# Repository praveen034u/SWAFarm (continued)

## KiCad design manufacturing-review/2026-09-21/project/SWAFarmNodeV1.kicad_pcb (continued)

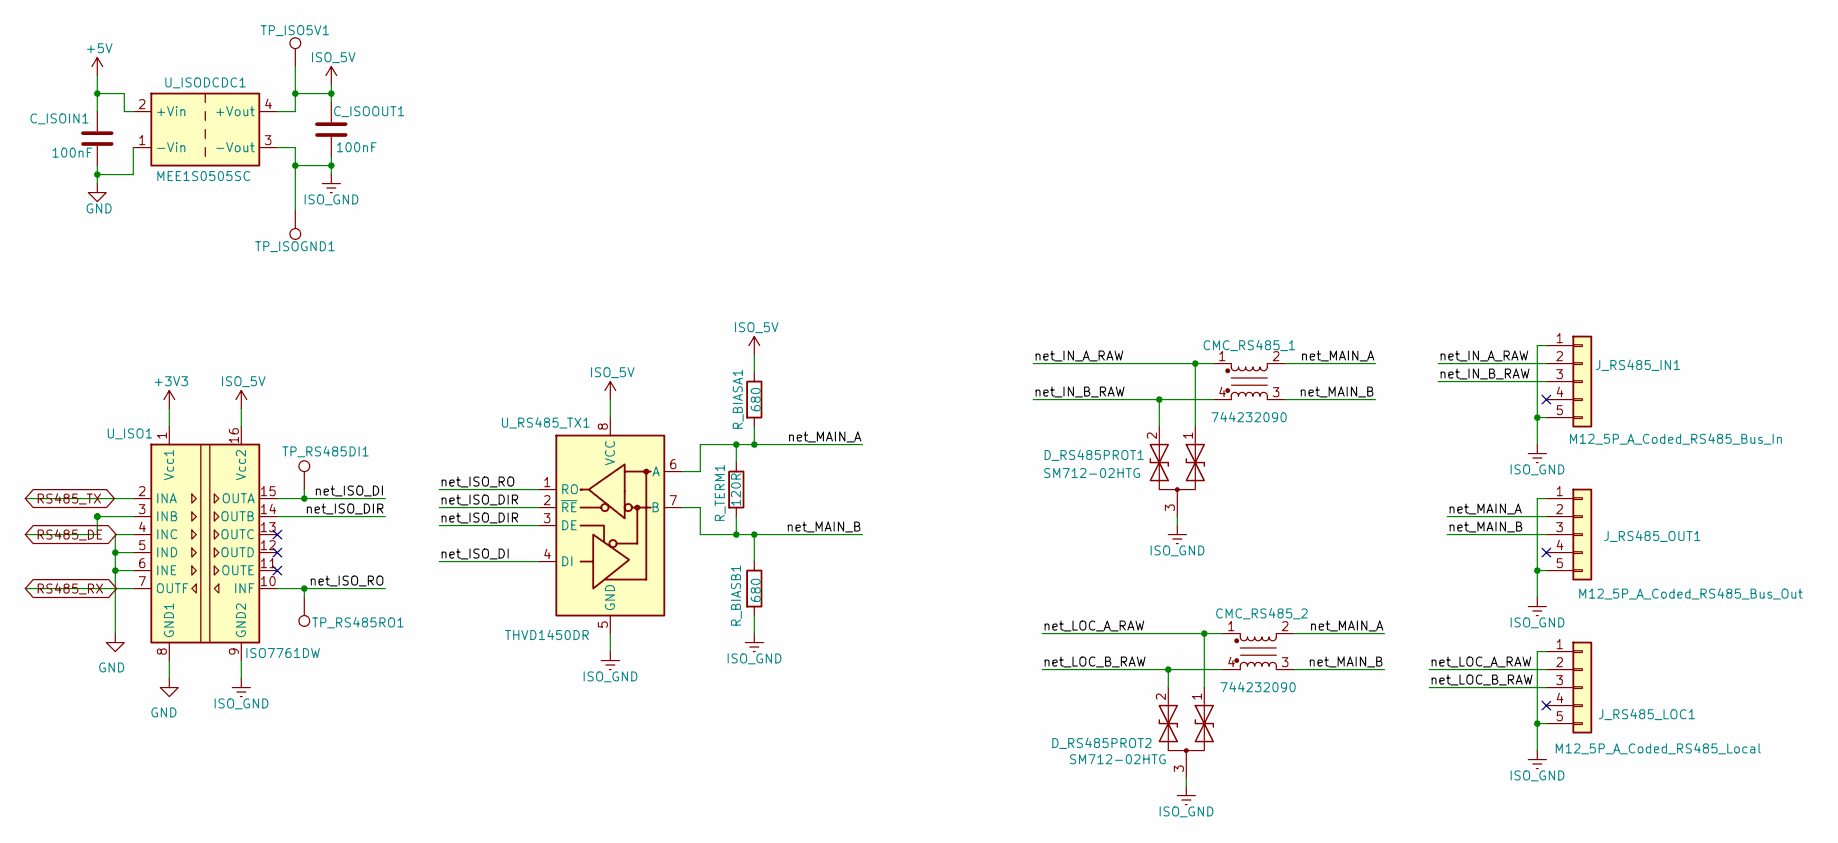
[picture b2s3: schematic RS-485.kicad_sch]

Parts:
CMC_RS485_1, CMC_RS485_2: 744232090; L_CommonMode_Wurth_WE-CNSW-1206; MPN 744232090
C_ISOIN1: 100nF; C_0603_1608Metric
C_ISOOUT1: 100nF; C_0603_1608Metric
D_RS485PROT1, D_RS485PROT2: SM712-02HTG; SOT-23
J_RS485_IN1: M12_5P_A_Coded_RS485_Bus_In; PinHeader_1x05_P2.54mm_Vertical
J_RS485_LOC1: M12_5P_A_Coded_RS485_Local; PinHeader_1x05_P2.54mm_Vertical
J_RS485_OUT1: M12_5P_A_Coded_RS485_Bus_Out; PinHeader_1x05_P2.54mm_Vertical
R_BIASA1: 680; R_0805_2012Metric
R_BIASB1: 680; R_0805_2012Metric
R_TERM1: 120R; R_0805_2012Metric
TP_ISO5V1: ISO_5V; TestPoint_Pad_D1.5mm
TP_ISOGND1: ISO_GND; TestPoint_Pad_D1.5mm
TP_RS485DI1: ISO_DI; TestPoint_Pad_D1.5mm
TP_RS485RO1: ISO_RO; TestPoint_Pad_D1.5mm
U_ISO1: ISO7761DW; SOIC-16W_7.5x10.3mm_P1.27mm
U_ISODCDC1: MEE1S0505SC; Converter_DCDC_Murata_MEE1SxxxxSC_THT
U_RS485_TX1: THVD1450DR; SOIC-8_3.9x4.9mm_P1.27mm

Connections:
+3V3: U_ISO1.1 (Vcc1); also elsewhere on the board
+5V: C_ISOIN1.1, U_ISODCDC1.2 (+Vin); also elsewhere on the board
/RS-485/net_IN_A_RAW: CMC_RS485_1.1, D_RS485PROT1.1 (A1), J_RS485_IN1.2
/RS-485/net_IN_B_RAW: CMC_RS485_1.4, D_RS485PROT1.2 (A2), J_RS485_IN1.3
/RS-485/net_ISO_DI: TP_RS485DI1.1 (1_1), U_ISO1.15 (OUTA), U_RS485_TX1.4 (DI)
/RS-485/net_ISO_DIR: U_ISO1.14 (OUTB), U_RS485_TX1.2 (~RE), U_RS485_TX1.3 (DE)
/RS-485/net_ISO_RO: TP_RS485RO1.1 (1_1), U_ISO1.10 (INF), U_RS485_TX1.1 (RO)
/RS-485/net_LOC_A_RAW: CMC_RS485_2.1, D_RS485PROT2.1 (A1), J_RS485_LOC1.2
/RS-485/net_LOC_B_RAW: CMC_RS485_2.4, D_RS485PROT2.2 (A2), J_RS485_LOC1.3
/RS-485/net_MAIN_A: CMC_RS485_1.2, CMC_RS485_2.2, J_RS485_OUT1.2, R_BIASA1.2, R_TERM1.1, U_RS485_TX1.6 (A)
/RS-485/net_MAIN_B: CMC_RS485_1.3, CMC_RS485_2.3, J_RS485_OUT1.3, R_BIASB1.1, R_TERM1.2, U_RS485_TX1.7 (B)
GND: C_ISOIN1.2, U_ISO1.4 (INC), U_ISO1.5 (IND), U_ISO1.6 (INE), U_ISO1.8 (GND1), U_ISODCDC1.1 (-Vin); also elsewhere on the board
ISO_5V: C_ISOOUT1.1, R_BIASA1.1, TP_ISO5V1.1 (1_1), U_ISO1.16 (Vcc2), U_ISODCDC1.4 (+Vout), U_RS485_TX1.8 (VCC)
ISO_GND: C_ISOOUT1.2, D_RS485PROT1.3 (common), D_RS485PROT2.3 (common), J_RS485_IN1.1, J_RS485_IN1.5, J_RS485_LOC1.1, J_RS485_LOC1.5, J_RS485_OUT1.1, J_RS485_OUT1.5, R_BIASB1.2, TP_ISOGND1.1 (1_1), U_ISO1.9 (GND2), U_ISODCDC1.3 (-Vout), U_RS485_TX1.5 (GND)
RS485_DE: U_ISO1.3 (INB); also elsewhere on the board
RS485_RX: U_ISO1.7 (OUTF); also elsewhere on the board
RS485_TX: U_ISO1.2 (INA); also elsewhere on the board

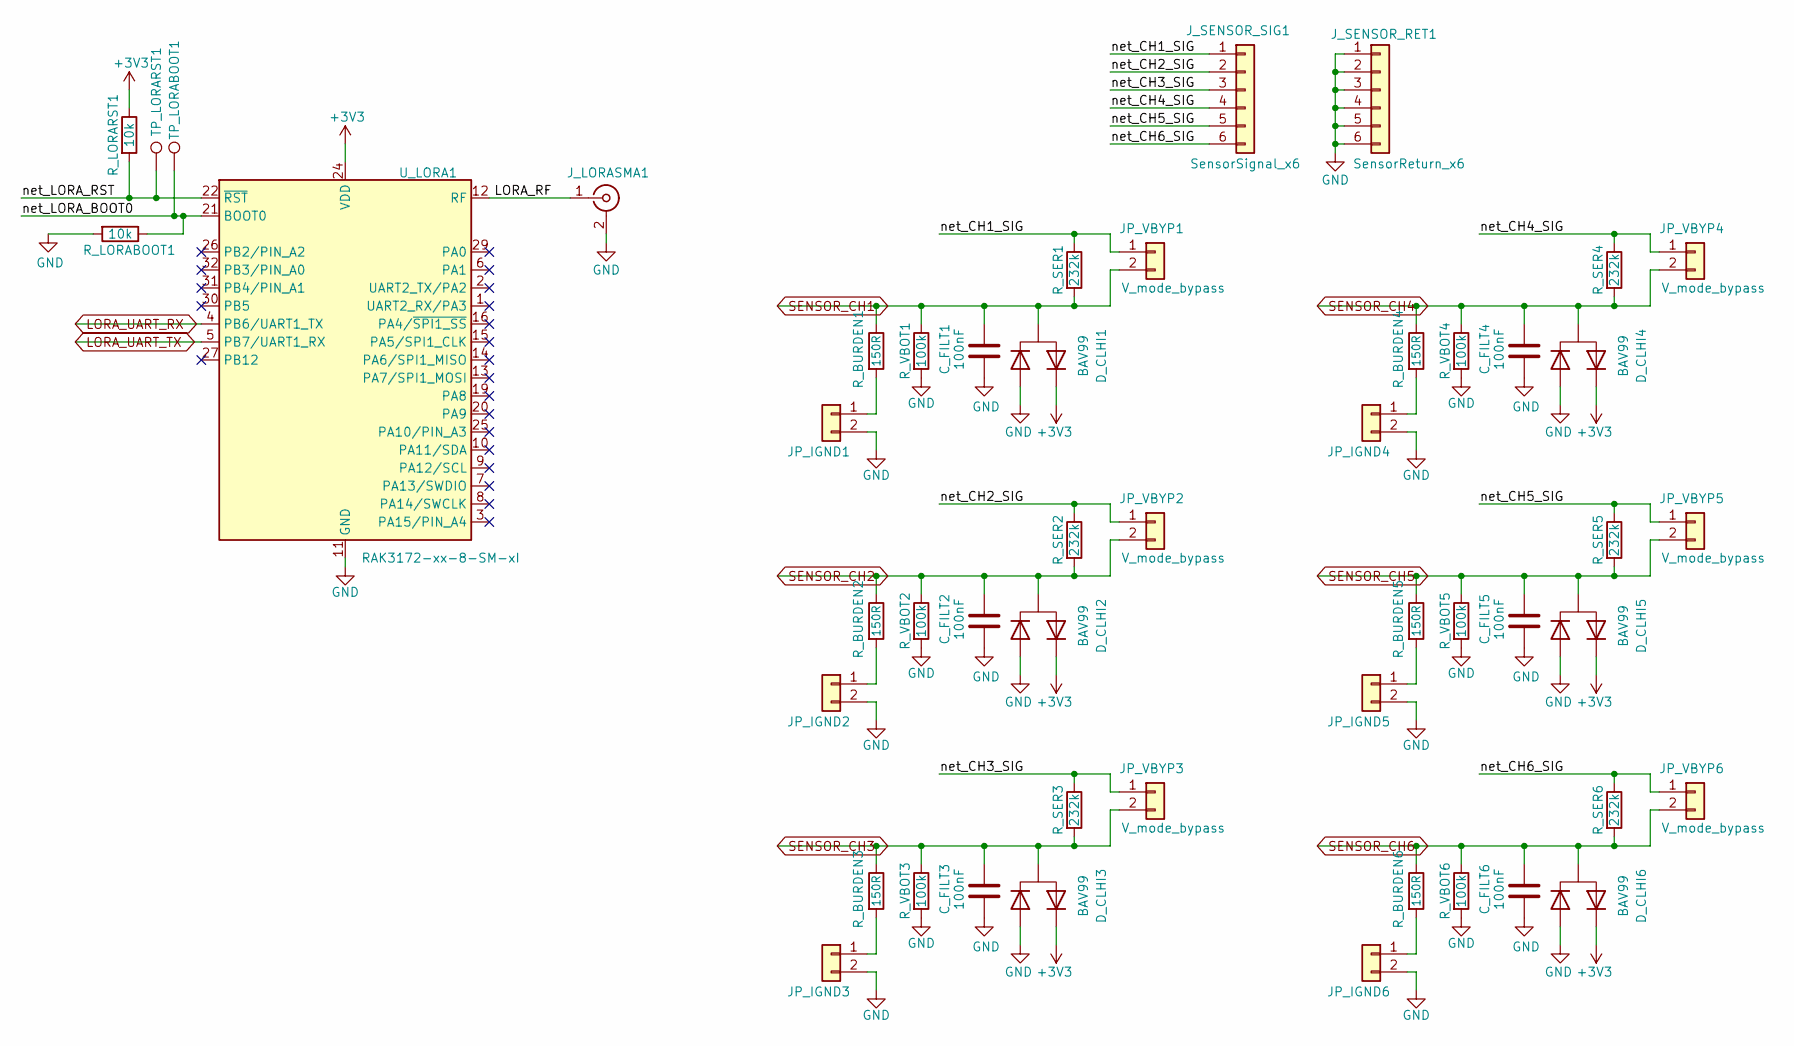
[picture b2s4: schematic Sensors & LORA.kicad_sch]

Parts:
C_FILT1, C_FILT2, C_FILT3, C_FILT4, C_FILT5, C_FILT6: 100nF; C_0603_1608Metric
D_CLHI1, D_CLHI2, D_CLHI3, D_CLHI4, D_CLHI5, D_CLHI6: BAV99; SOT-23; MPN BAV99LT1G
JP_IGND1, JP_IGND2, JP_IGND3, JP_IGND4, JP_IGND5, JP_IGND6: I_mode_gnd; PinHeader_1x02_P2.54mm_Vertical
JP_VBYP1, JP_VBYP2, JP_VBYP3, JP_VBYP4, JP_VBYP5, JP_VBYP6: V_mode_bypass; PinHeader_1x02_P2.54mm_Vertical
J_LORASMA1: SMA_Bulkhead_Antenna; SMA_Amphenol_132134_Vertical
J_SENSOR_RET1: SensorReturn_x6; TerminalBlock_Phoenix_MKDS-1,5-6-5.08_1x06_P5.08mm_Horizont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
J_SENSOR_SIG1: SensorSignal_x6; TerminalBlock_Phoenix_MKDS-1,5-6-5.08_1x06_P5.08mm_Horizont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
R_BURDEN1, R_BURDEN2, R_BURDEN3, R_BURDEN4, R_BURDEN5, R_BURDEN6: 150R; R_0805_2012Metric
R_LORABOOT1: 10k; R_0805_2012Metric
R_LORARST1: 10k; R_0805_2012Metric
R_SER1, R_SER2, R_SER3, R_SER4, R_SER5, R_SER6: 232k; R_0805_2012Metric
R_VBOT1, R_VBOT2, R_VBOT3, R_VBOT4, R_VBOT5, R_VBOT6: 100k; R_0805_2012Metric
TP_LORABOOT1: LORA_BOOT0; TestPoint_Pad_D1.5mm
TP_LORARST1: LORA_RESET; TestPoint_Pad_D1.5mm
U_LORA1: RAK3172-xx-8-SM-xI; RAK3172

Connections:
+3V3: D_CLHI1.2 (S), D_CLHI2.2 (S), D_CLHI3.2 (S), D_CLHI4.2 (S), D_CLHI5.2 (S), D_CLHI6.2 (S), R_LORARST1.1, U_LORA1.24 (VDD); also elsewhere on the board
/Sensors & LORA/LORA_RF: J_LORASMA1.1 (In), U_LORA1.12 (RF)
/Sensors & LORA/net_CH1_SIG: JP_VBYP1.1, J_SENSOR_SIG1.1, R_SER1.1
/Sensors & LORA/net_CH2_SIG: JP_VBYP2.1, J_SENSOR_SIG1.2, R_SER2.1
/Sensors & LORA/net_CH3_SIG: JP_VBYP3.1, J_SENSOR_SIG1.3, R_SER3.1
/Sensors & LORA/net_CH4_SIG: JP_VBYP4.1, J_SENSOR_SIG1.4, R_SER4.1
/Sensors & LORA/net_CH5_SIG: JP_VBYP5.1, J_SENSOR_SIG1.5, R_SER5.1
/Sensors & LORA/net_CH6_SIG: JP_VBYP6.1, J_SENSOR_SIG1.6, R_SER6.1
/Sensors & LORA/net_LORA_BOOT0: R_LORABOOT1.1, TP_LORABOOT1.1 (1_1), U_LORA1.21 (BOOT0)
/Sensors & LORA/net_LORA_RST: R_LORARST1.2, TP_LORARST1.1 (1_1), U_LORA1.22 (~RST)
GND: C_FILT1.2, C_FILT2.2, C_FILT3.2, C_FILT4.2, C_FILT5.2, C_FILT6.2, D_CLHI1.1 (G), D_CLHI2.1 (G), D_CLHI3.1 (G), D_CLHI4.1 (G), D_CLHI5.1 (G), D_CLHI6.1 (G), JP_IGND1.2, JP_IGND2.2, JP_IGND3.2, JP_IGND4.2, JP_IGND5.2, JP_IGND6.2, J_LORASMA1.2 (Ext), J_SENSOR_RET1.1, J_SENSOR_RET1.2, J_SENSOR_RET1.3, J_SENSOR_RET1.4, J_SENSOR_RET1.5, J_SENSOR_RET1.6, R_LORABOOT1.2, R_VBOT1.2, R_VBOT2.2, R_VBOT3.2, R_VBOT4.2, R_VBOT5.2, R_VBOT6.2, U_LORA1.11 (GND), U_LORA1.17 (GND), U_LORA1.18 (GND), U_LORA1.23 (GND), U_LORA1.28 (GND); also elsewhere on the board
LORA_UART_RX: U_LORA1.4 (PB6/UART1_TX); also elsewhere on the board
LORA_UART_TX: U_LORA1.5 (PB7/UART1_RX); also elsewhere on the board
unnamed: JP_IGND1.1, R_BURDEN1.2
unnamed: JP_IGND2.1, R_BURDEN2.2
unnamed: JP_IGND3.1, R_BURDEN3.2
unnamed: JP_IGND4.1, R_BURDEN4.2
unnamed: JP_IGND5.1, R_BURDEN5.2
unnamed: JP_IGND6.1, R_BURDEN6.2
SENSOR_CH1: C_FILT1.1, D_CLHI1.3 (D), JP_VBYP1.2, R_BURDEN1.1, R_SER1.2, R_VBOT1.1; also elsewhere on the board
SENSOR_CH2: C_FILT2.1, D_CLHI2.3 (D), JP_VBYP2.2, R_BURDEN2.1, R_SER2.2, R_VBOT2.1; also elsewhere on the board
SENSOR_CH3: C_FILT3.1, D_CLHI3.3 (D), JP_VBYP3.2, R_BURDEN3.1, R_SER3.2, R_VBOT3.1; also elsewhere on the board
SENSOR_CH4: C_FILT4.1, D_CLHI4.3 (D), JP_VBYP4.2, R_BURDEN4.1, R_SER4.2, R_VBOT4.1; also elsewhere on the board
SENSOR_CH5: C_FILT5.1, D_CLHI5.3 (D), JP_VBYP5.2, R_BURDEN5.1, R_SER5.2, R_VBOT5.1; also elsewhere on the board
SENSOR_CH6: C_FILT6.1, D_CLHI6.3 (D), JP_VBYP6.2, R_BURDEN6.1, R_SER6.2, R_VBOT6.1; also elsewhere on the board

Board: 4 copper layers, 185 parts (0 on the bottom side), 119 nets, no tracks yet.

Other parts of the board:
C_BULK2: 10uF; C_1206_3216Metric
C_DEC1, C_DEC2, C_DEC3, C_DEC4, C_DEC5, C_DEC6, C_DEC7, C_DEC8, C_DEC9, C_DEC10: 100nF; C_0603_1608Metric
C_EN1: 1uF; C_0805_2012Metric
D_FLT1: Red; LED_0805_2012Metric
D_LINK1: Yellow; LED_0805_2012Metric
D_PWR1: Green; LED_0805_2012Metric
J_PROG1: Debug_UART_TX_RX_GND; PinHeader_1x03_P2.54mm_Vertical
MH1, MH2, MH3, MH4: MountingHole_3.2mm_M3
R_BOOT1: 10k; R_0805_2012Metric
R_ENPU1: 10k; R_0805_2012Metric
R_LEDFLT1: 1k; R_0805_2012Metric
R_LINK1: 1k; R_0805_2012Metric
R_PWR1: 1k; R_0805_2012Metric
R_SETUP1: 10k; R_0805_2012Metric
SW_BOOT1: BOOT; SW_SPST_B3U-1000P
SW_RESET1: RESET; SW_SPST_B3U-1000P
SW_SETUP1: SETUP; SW_SPST_B3U-1000P
U_MCU1: ESP32-S3-WROOM-1-N16R8; ESP32-S3-WROOM-1

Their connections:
+3V3: C_BULK2.1, C_DEC1.1, C_DEC2.1, C_DEC3.1, C_DEC4.1, C_DEC5.1, C_DEC6.1, C_DEC7.1, C_DEC8.1, C_DEC9.1, C_DEC10.1, R_BOOT1.1, R_ENPU1.1, R_SETUP1.1, U_MCU1.2 (3V3); also elsewhere on the board
/MCU/LED_FAULT: R_LEDFLT1.1, U_MCU1.33 (IO40)
/MCU/LED_LINK: R_LINK1.1, U_MCU1.32 (IO39)
/MCU/LED_PWR: R_PWR1.1, U_MCU1.31 (IO38)
/MCU/SETUP_BTN: R_SETUP1.2, SW_SETUP1.1, U_MCU1.22 (IO14)
/MCU/net_BOOT: R_BOOT1.2, SW_BOOT1.1, U_MCU1.27 (IO0)
/MCU/net_CHIP_EN: C_EN1.1, R_ENPU1.2, SW_RESET1.1, U_MCU1.3 (EN)
/MCU/net_DEBUG_RX: J_PROG1.2, U_MCU1.36 (RXD0)
/MCU/net_DEBUG_TX: J_PROG1.1, U_MCU1.37 (TXD0)
GND: C_BULK2.2, C_DEC1.2, C_DEC2.2, C_DEC3.2, C_DEC4.2, C_DEC5.2, C_DEC6.2, C_DEC7.2, C_DEC8.2, C_DEC9.2, C_DEC10.2, C_EN1.2, D_FLT1.1 (K), D_LINK1.1 (K), D_PWR1.1 (K), J_PROG1.3, SW_BOOT1.2, SW_RESET1.2, SW_SETUP1.2, U_MCU1.1 (GND), U_MCU1.40 (GND), U_MCU1.41 (GND); also elsewhere on the board
LORA_UART_RX: U_MCU1.11 (IO18); also elsewhere on the board
LORA_UART_TX: U_MCU1.10 (IO17); also elsewhere on the board
unnamed: D_FLT1.2 (A), R_LEDFLT1.2
unnamed: D_LINK1.2 (A), R_LINK1.2
unnamed: D_PWR1.2 (A), R_PWR1.2
RS485_DE: U_MCU1.34 (IO41); also elsewhere on the board
RS485_RX: U_MCU1.9 (IO16); also elsewhere on the board
RS485_TX: U_MCU1.8 (IO15); also elsewhere on the board
SENSOR_CH1: U_MCU1.39 (IO1); also elsewhere on the board
SENSOR_CH2: U_MCU1.38 (IO2); also elsewhere on the board
SENSOR_CH3: U_MCU1.4 (IO4); also elsewhere on the board
SENSOR_CH4: U_MCU1.5 (IO5); also elsewhere on the board
SENSOR_CH5: U_MCU1.6 (IO6); also elsewhere on the board
SENSOR_CH6: U_MCU1.7 (IO7); also elsewhere on the board
VALVE_SPI_CS: U_MCU1.18 (IO10); also elsewhere on the board
VALVE_SPI_MISO: U_MCU1.21 (IO13); also elsewhere on the board
VALVE_SPI_MOSI: U_MCU1.19 (IO11); also elsewhere on the board
VALVE_SPI_SCLK: U_MCU1.20 (IO12); also elsewhere on the board
net_USB_DM: U_MCU1.13 (USB_D-); also elsewhere on the board
net_USB_DP: U_MCU1.14 (USB_D+); also elsewhere on the board
